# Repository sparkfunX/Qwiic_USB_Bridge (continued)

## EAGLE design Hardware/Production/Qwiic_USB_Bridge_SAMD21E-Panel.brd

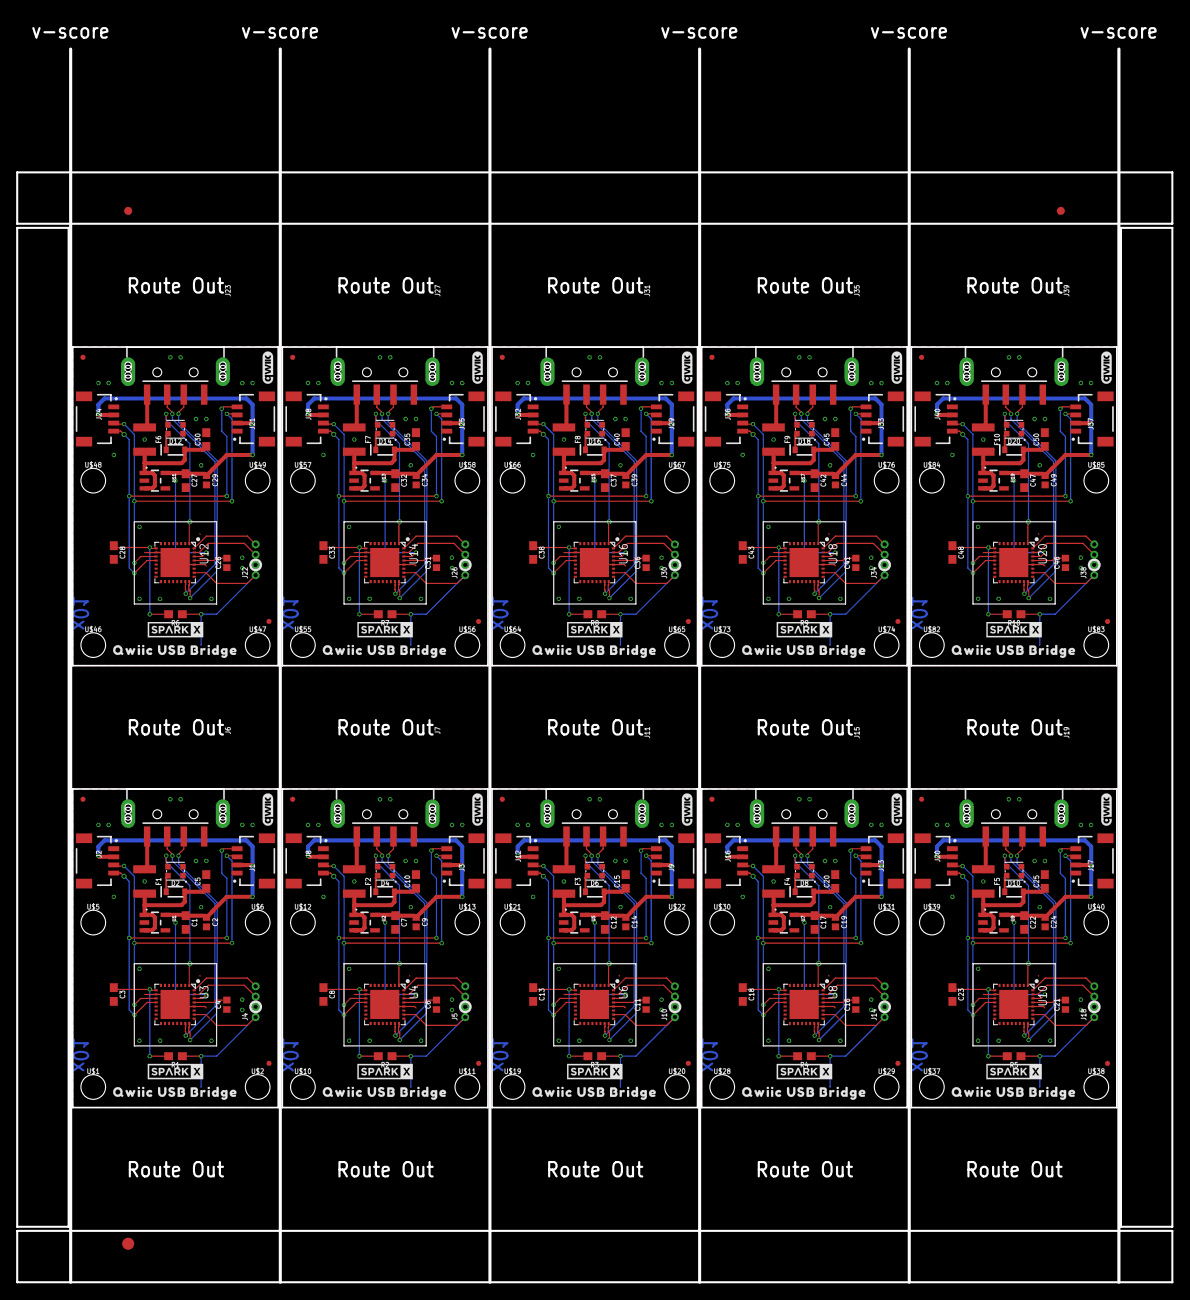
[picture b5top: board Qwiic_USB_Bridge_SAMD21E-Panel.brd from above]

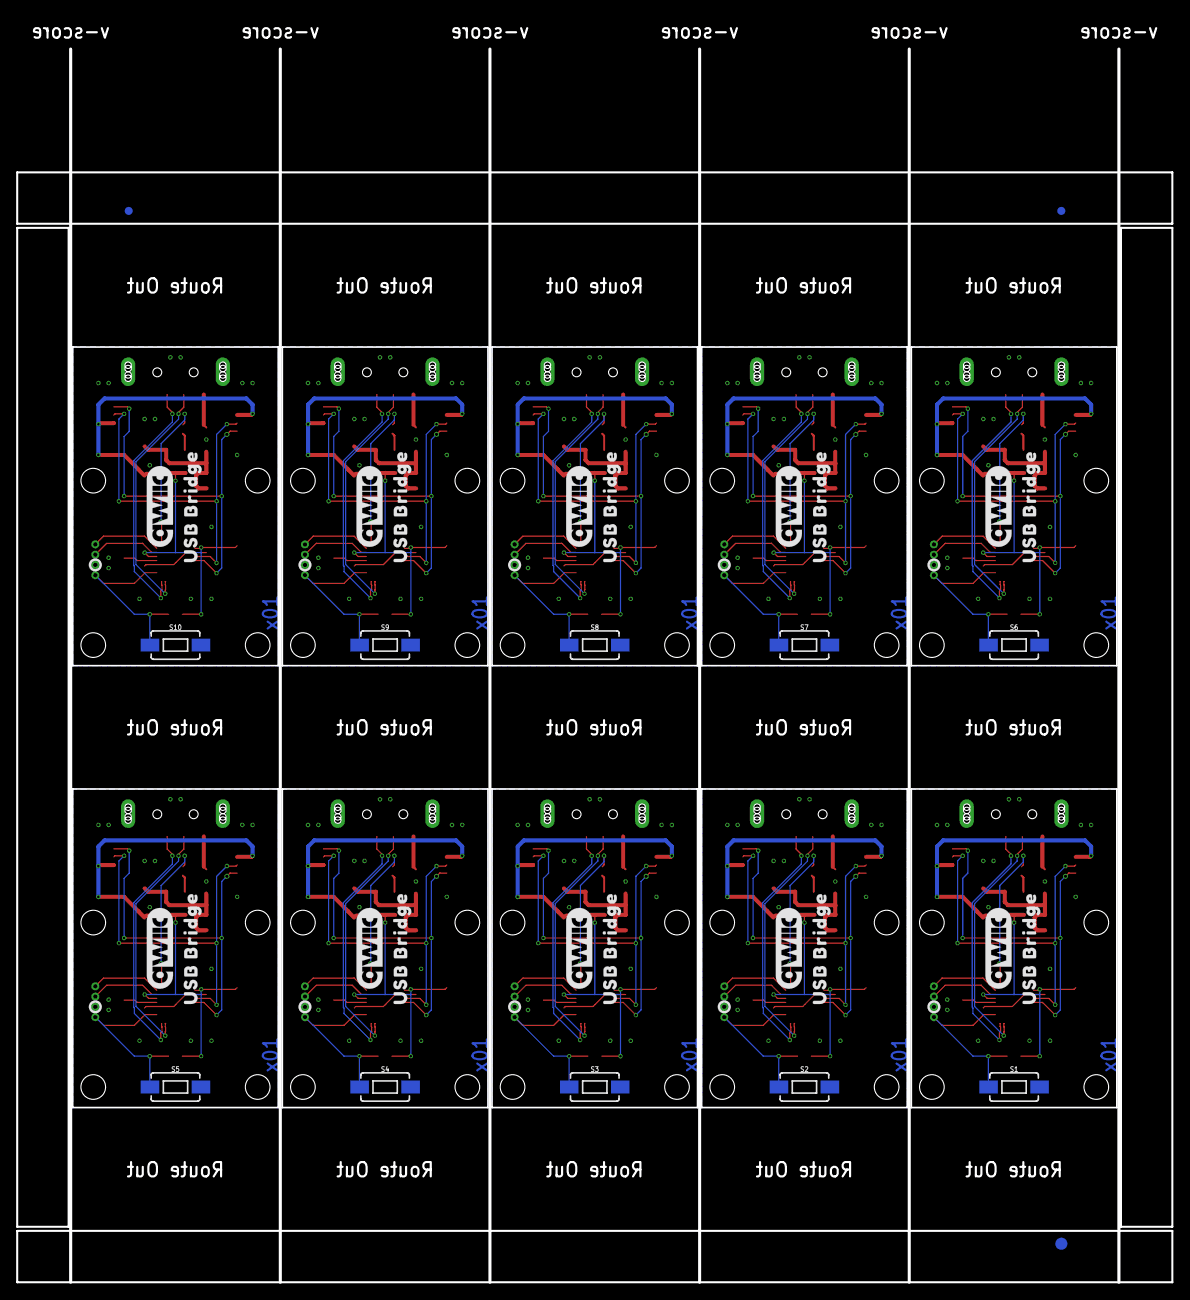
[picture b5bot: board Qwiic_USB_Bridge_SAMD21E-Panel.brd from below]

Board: 2 copper layers, 142.6 x 156.3 mm, 276 parts (33 on the bottom side), 140 nets.

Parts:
C1, C3, C7, C8, C12, C13, C17, C18, C22, C23, C27, C28, C32, C33, C37, C38, C42, C43, C47, C48: 10uF; 0603
C2, C4, C6, C9, C11, C14, C16, C19, C21, C24, C26, C29, C31, C34, C36, C39, C41, C44, C46, C49: 1.0uF; 0402
C5, C10, C15, C20, C25, C30, C35, C40, C45, C50: 0.1uF; 0603
D1, D3, D5, D7, D9, D11, D13, D15, D17, D19: WS2812_2020; WS2812-2020
D2, D4, D6, D8, D10, D12, D14, D16, D18, D20: 250mA/100V; SOD-323
E$1, E$2, E$3, E$4: FIDUCIAL-1X2
E$5, E$6: FIDUCIAL-1.5X3
F1, F2, F3, F4, F5, F6, F7, F8, F9, F10: 6V/2A; 1210
FD1, FD2, FD3, FD4, FD5, FD6, FD7, FD8, FD9, FD10, FD11, FD12, FD13, FD14, FD15, FD16, FD17, FD18, FD19, FD20: FIDUCIALUFIDUCIAL; FIDUCIAL-MICRO
J1, J2, J3, J8, J9, J12, J13, J16, J17, J20, J21, J24, J25, J28, J29, J32, J33, J36, J37, J40: QWIIC_RIGHT_ANGLE; JST04_1MM_RA
J4, J5, J10, J14, J18, J22, J26, J30, J34, J38: 1X04_1.27MM_NO_SILK
J6, J7, J11, J15, J19, J23, J27, J31, J35, J39: USB_A_SMT_MALE; USB-A-SMT-MALE
R1, R2, R3, R4, R5, R6, R7, R8, R9, R10: 10k; 0603
S1, S2, S3, S4, S5, S6, S7, S8, S9, S10: MOMENTARY-SWITCH-SPST-SMD-6.0X3.5MM; TACTILE_SWITCH_SMD_6.0X3.5MM
U1, U2, U5, U7, U9, U11, U13, U15, U17, U19: 3.3V; SOT23-5
U3, U4, U6, U8, U10, U12, U14, U16, U18, U20: ATSAMD21E18A-U; QFN-32_SAMD
U$1, U$2, U$5, U$6, U$10, U$11, U$12, U$13, U$19, U$20, U$21, U$22, U$28, U$29, U$30, U$31, U$37, U$38, U$39, U$40, U$46, U$47, U$48, U$49, U$55, U$56, U$57, U$58, U$64, U$65, U$66, U$67, U$73, U$74, U$75, U$76, U$82, U$83, U$84, U$85: STAND-OFF-TIGHT
U$3, U$14, U$23, U$32, U$41, U$50, U$59, U$68, U$77, U$86: QWIIC_USB_BRIDGE0
U$4, U$15, U$24, U$33, U$42, U$51, U$60, U$69, U$78, U$87: SPARKX-SMALL
U$7, U$16, U$25, U$34, U$43, U$52, U$61, U$70, U$79, U$88: QWIIC_10MM
U$8, U$17, U$26, U$35, U$44, U$53, U$62, U$71, U$80, U$89: USB_BRIDGE0
U$9, U$18, U$27, U$36, U$45, U$54, U$63, U$72, U$81, U$90: QWIIC_4MM

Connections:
3.3V: C1.1, C2.1, C3.1, J1.2, J2.2, R1.2, U1.5, U3.VDD, U3.VDDIN
3.3V1: C7.1, C8.1, C9.1, J3.2, J8.2, R2.2, U2.5, U4.VDD, U4.VDDIN
3.3V2: C12.1, C13.1, C14.1, J9.2, J12.2, R3.2, U5.5, U6.VDD, U6.VDDIN
3.3V3: C17.1, C18.1, C19.1, J13.2, J16.2, R4.2, U7.5, U8.VDD, U8.VDDIN
3.3V4: C22.1, C23.1, C24.1, J17.2, J20.2, R5.2, U9.5, U10.VDD, U10.VDDIN
3.3V5: C27.1, C28.1, C29.1, J21.2, J24.2, R6.2, U11.5, U12.VDD, U12.VDDIN
3.3V6: C32.1, C33.1, C34.1, J25.2, J28.2, R7.2, U13.5, U14.VDD, U14.VDDIN
3.3V7: C37.1, C38.1, C39.1, J29.2, J32.2, R8.2, U15.5, U16.VDD, U16.VDDIN
3.3V8: C42.1, C43.1, C44.1, J33.2, J36.2, R9.2, U17.5, U18.VDD, U18.VDDIN
3.3V9: C47.1, C48.1, C49.1, J37.2, J40.2, R10.2, U19.5, U20.VDD, U20.VDDIN
!RESET: J4.1, R1.1, S1.1, U3.RES
!RESET1: J5.1, R2.1, S2.1, U4.RES
!RESET2: J10.1, R3.1, S3.1, U6.RES
!RESET3: J14.1, R4.1, S4.1, U8.RES
!RESET4: J18.1, R5.1, S5.1, U10.RES
!RESET5: J22.1, R6.1, S6.1, U12.RES
!RESET6: J26.1, R7.1, S7.1, U14.RES
!RESET7: J30.1, R8.1, S8.1, U16.RES
!RESET8: J34.1, R9.1, S9.1, U18.RES
!RESET9: J38.1, R10.1, S10.1, U20.RES
GND: C1.2, C2.2, C3.2, C4.1, C5.2, D1.GND, J1.1, J2.1, J4.2, J6.GND1, J6.SHLD1, J6.SHLD2, S1.2, U1.2, U3.GND, U3.GNDANA, U3.PAD
GND1: C6.1, C7.2, C8.2, C9.2, C10.2, D3.GND, J3.1, J5.2, J7.GND1, J7.SHLD1, J7.SHLD2, J8.1, S2.2, U2.2, U4.GND, U4.GNDANA, U4.PAD
GND2: C11.1, C12.2, C13.2, C14.2, C15.2, D5.GND, J9.1, J10.2, J11.GND1, J11.SHLD1, J11.SHLD2, J12.1, S3.2, U5.2, U6.GND, U6.GNDANA, U6.PAD
GND3: C16.1, C17.2, C18.2, C19.2, C20.2, D7.GND, J13.1, J14.2, J15.GND1, J15.SHLD1, J15.SHLD2, J16.1, S4.2, U7.2, U8.GND, U8.GNDANA, U8.PAD
GND4: C21.1, C22.2, C23.2, C24.2, C25.2, D9.GND, J17.1, J18.2, J19.GND1, J19.SHLD1, J19.SHLD2, J20.1, S5.2, U9.2, U10.GND, U10.GNDANA, U10.PAD
GND5: C26.1, C27.2, C28.2, C29.2, C30.2, D11.GND, J21.1, J22.2, J23.GND1, J23.SHLD1, J23.SHLD2, J24.1, S6.2, U11.2, U12.GND, U12.GNDANA, U12.PAD
GND6: C31.1, C32.2, C33.2, C34.2, C35.2, D13.GND, J25.1, J26.2, J27.GND1, J27.SHLD1, J27.SHLD2, J28.1, S7.2, U13.2, U14.GND, U14.GNDANA, U14.PAD
GND7: C36.1, C37.2, C38.2, C39.2, C40.2, D15.GND, J29.1, J30.2, J31.GND1, J31.SHLD1, J31.SHLD2, J32.1, S8.2, U15.2, U16.GND, U16.GNDANA, U16.PAD
GND8: C41.1, C42.2, C43.2, C44.2, C45.2, D17.GND, J33.1, J34.2, J35.GND1, J35.SHLD1, J35.SHLD2, J36.1, S9.2, U17.2, U18.GND, U18.GNDANA, U18.PAD
GND9: C46.1, C47.2, C48.2, C49.2, C50.2, D19.GND, J37.1, J38.2, J39.GND1, J39.SHLD1, J39.SHLD2, J40.1, S10.2, U19.2, U20.GND, U20.GNDANA, U20.PAD
LED_IN: D1.DI, U3.PA00
LED_IN1: D3.DI, U4.PA00
LED_IN2: D5.DI, U6.PA00
LED_IN3: D7.DI, U8.PA00
LED_IN4: D9.DI, U10.PA00
LED_IN5: D11.DI, U12.PA00
LED_IN6: D13.DI, U14.PA00
LED_IN7: D15.DI, U16.PA00
LED_IN8: D17.DI, U18.PA00
LED_IN9: D19.DI, U20.PA00
unnamed: F1.1, J6.VBUS1
unnamed: D1.VCC, D2.C
unnamed: D3.VCC, D4.C
unnamed: F2.1, J7.VBUS1
unnamed: D5.VCC, D6.C
unnamed: F3.1, J11.VBUS1
unnamed: D7.VCC, D8.C
unnamed: F4.1, J15.VBUS1
unnamed: D9.VCC, D10.C
unnamed: F5.1, J19.VBUS1
unnamed: D11.VCC, D12.C
unnamed: F6.1, J23.VBUS1
unnamed: D13.VCC, D14.C
unnamed: F7.1, J27.VBUS1
unnamed: D15.VCC, D16.C
unnamed: F8.1, J31.VBUS1
unnamed: D17.VCC, D18.C
unnamed: F9.1, J35.VBUS1
unnamed: D19.VCC, D20.C
unnamed: F10.1, J39.VBUS1
SCL: J1.4, J2.4, U3.PA09
SCL1: J3.4, J8.4, U4.PA09
SCL2: J9.4, J12.4, U6.PA09
SCL3: J13.4, J16.4, U8.PA09
SCL4: J17.4, J20.4, U10.PA09
SCL5: J21.4, J24.4, U12.PA09
SCL6: J25.4, J28.4, U14.PA09
SCL7: J29.4, J32.4, U16.PA09
SCL8: J33.4, J36.4, U18.PA09
SCL9: J37.4, J40.4, U20.PA09
SDA: J1.3, J2.3, U3.PA08
SDA1: J3.3, J8.3, U4.PA08
SDA2: J9.3, J12.3, U6.PA08
SDA3: J13.3, J16.3, U8.PA08
SDA4: J17.3, J20.3, U10.PA08
SDA5: J21.3, J24.3, U12.PA08
SDA6: J25.3, J28.3, U14.PA08
SDA7: J29.3, J32.3, U16.PA08
SDA8: J33.3, J36.3, U18.PA08
SDA9: J37.3, J40.3, U20.PA08
SWCLK: J4.3, U3.PA30
SWCLK1: J5.3, U4.PA30
SWCLK2: J10.3, U6.PA30
SWCLK3: J14.3, U8.PA30
SWCLK4: J18.3, U10.PA30
SWCLK5: J22.3, U12.PA30
SWCLK6: J26.3, U14.PA30
SWCLK7: J30.3, U16.PA30
SWCLK8: J34.3, U18.PA30
SWCLK9: J38.3, U20.PA30
SWDIO: J4.4, U3.PA31
SWDIO1: J5.4, U4.PA31
SWDIO2: J10.4, U6.PA31
SWDIO3: J14.4, U8.PA31
SWDIO4: J18.4, U10.PA31
SWDIO5: J22.4, U12.PA31
SWDIO6: J26.4, U14.PA31
SWDIO7: J30.4, U16.PA31
SWDIO8: J34.4, U18.PA31
SWDIO9: J38.4, U20.PA31
USB_N: J6.D-1, U3.PA24
USB_N1: J7.D-1, U4.PA24
USB_N2: J11.D-1, U6.PA24
USB_N3: J15.D-1, U8.PA24
USB_N4: J19.D-1, U10.PA24
USB_N5: J23.D-1, U12.PA24
USB_N6: J27.D-1, U14.PA24
USB_N7: J31.D-1, U16.PA24
USB_N8: J35.D-1, U18.PA24
USB_N9: J39.D-1, U20.PA24
USB_P: J6.D+1, U3.PA25
USB_P1: J7.D+1, U4.PA25
USB_P2: J11.D+1, U6.PA25
USB_P3: J15.D+1, U8.PA25
USB_P4: J19.D+1, U10.PA25
USB_P5: J23.D+1, U12.PA25
USB_P6: J27.D+1, U14.PA25
USB_P7: J31.D+1, U16.PA25
USB_P8: J35.D+1, U18.PA25
USB_P9: J39.D+1, U20.PA25
VDDCORE: C4.2, U3.VDDCORE
VDDCORE1: C6.2, U4.VDDCORE
VDDCORE2: C11.2, U6.VDDCORE
VDDCORE3: C16.2, U8.VDDCORE
VDDCORE4: C21.2, U10.VDDCORE
VDDCORE5: C26.2, U12.VDDCORE
VDDCORE6: C31.2, U14.VDDCORE
VDDCORE7: C36.2, U16.VDDCORE
VDDCORE8: C41.2, U18.VDDCORE
VDDCORE9: C46.2, U20.VDDCORE
VIN: C5.1, D2.A, F1.2, U1.1, U1.3
VIN1: C10.1, D4.A, F2.2, U2.1, U2.3
VIN2: C15.1, D6.A, F3.2, U5.1, U5.3
VIN3: C20.1, D8.A, F4.2, U7.1, U7.3
VIN4: C25.1, D10.A, F5.2, U9.1, U9.3
VIN5: C30.1, D12.A, F6.2, U11.1, U11.3
VIN6: C35.1, D14.A, F7.2, U13.1, U13.3
VIN7: C40.1, D16.A, F8.2, U15.1, U15.3
VIN8: C45.1, D18.A, F9.2, U17.1, U17.3
VIN9: C50.1, D20.A, F10.2, U19.1, U19.3

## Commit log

2021-10-21 PCB x01 protos on order
2022-04-08 Proto Revision
    Swap out ATSAMD21E for 21G TQFP
2022-08-22 Updating to build version
2023-11-07 Remove Firmware Directory and Update Mechanicals
2023-11-07 Add Schematic PDF
2024-01-11 Add programming batch file
